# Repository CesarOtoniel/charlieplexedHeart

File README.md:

# charlieplexedHeart

Charlieplexed LED sequencer with the shape of a heart
___
Board:

___
Proposed layout:

___
The finished project:
[![IMAGE ALT TEXT HERE]](https://youtube.com/shorts/6VQt6mm0j_k?si=q3w5lvo53maSrrU2)

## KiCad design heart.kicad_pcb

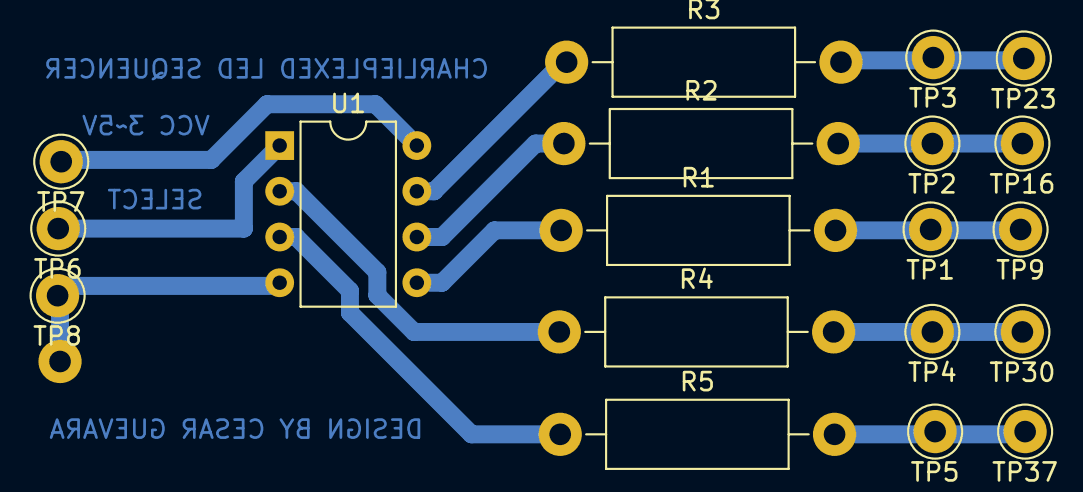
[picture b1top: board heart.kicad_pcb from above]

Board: 2 copper layers, 19 parts (0 on the bottom side), 13 nets.

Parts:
R1, R2, R3, R4, R5: R; R_Axial_DIN0411_L9.9mm_D3.6mm_P15.24mm_Horizontal
TP1, TP2, TP3, TP4, TP5, TP6, TP7, TP8, TP9, TP16, TP23, TP30, TP37: TestPoint; Pin_D1.0mm_L10.0mm_LooseFit
U1: ATtiny13A-P; DIP-8_W7.62mm

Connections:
GNDREF: TP8.1, U1.4 (GND)
unnamed: R2.2, TP2.1, TP16.1
unnamed: R1.2, TP1.1, TP9.1
unnamed: R3.2, TP3.1, TP23.1
unnamed: R4.2, TP4.1, TP30.1
unnamed: R5.2, TP5.1, TP37.1
unnamed: TP6.1, U1.1 (~RESET/PB5)
unnamed: R1.1, U1.5 (PB0)
unnamed: R2.1, U1.6 (PB1)
unnamed: R3.1, U1.7 (PB2)
unnamed: R4.1, U1.2 (PB3)
unnamed: R5.1, U1.3 (PB4)
VCC: TP7.1, U1.8 (VCC)

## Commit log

2024-02-27 Uploaded files with the finished project in Kicad.
2024-02-27 Create heart.c
    Program for ARDUINO/MPLABX
2024-02-27 Changed two bad connections on LED.
2024-03-06 Update README.md
    Updates to README
